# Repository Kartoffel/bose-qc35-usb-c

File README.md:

# Bose QC35 USB-C mod

This is a repository holding details of how to modify the Bose QC35 headphones
to support USB charging/firmware update over USB-C, rather than the archaic
micro-USB connector. This mod works with both QC35 I and QC35 II versions of the
headphones.

## Disclaimer

This mod involves opening and disassembing your rather expensive headphone that
you probably really like using. There is a not insignificant chance of you could
damaging your headphones in this process. Keep that in mind before you start.
For best chances of success: take your time, work on a well lit anti-static
workspace.

We don't take any responsibility nor liability for damage when using any
information provided in this repository.

Good luck!

## Quick start

### [View schematic and layout online using KiCanvas!](https://kicanvas.org/?github=https%3A%2F%2Fgithub.com%2Fjamesturton%2Fbose-qc35-usb-c)

## How to get started

You will be replacing the USB daughter board with a new one featuring a USB-C
connector. This means there is no modification to the existing USB daughter
board, thus (other than enlarging the hole in the plastic housing) this process
is easily reversible.

The exisiting USB daughter board has been reverse-engineered and it's schematic
has been drawn using KiCad 8.0. All of the source files are provided here if you
would like to make any more changes, however the [gerber files](https://github.com/jamesturton/bose-qc35-usb-c/blob/main/gerber.zip?raw=true)
are also provided which can be sent directly to the PCB fab of your choosing.
The thickness of the PCB should be 1mm.

Once you have the sent off for the PCB to be manufactured, you will need to
order the parts to populate the PCB with. Some PCB fabs offer assembly also, but
I am not sure if any 'budget' PCB fab offer double-sided assembly services.
An 'interactive BoM' can be found in the 'bom' directory.

## Assembly

Assembly of this PCB is not for the faint of heart. A decent soldering/re-work
station, microscope and experience with soldering fine-pitch components are all
recommended. The molex connector for the flat-flex to the main board has a pin
pitch of 0.4mm. I recommend starting with the passives and LEDs first, working
up to the larger ICs and connectors later.

Once you have assembled the PCB you can start to disassemble your headphones to
replace the USB daughter board:
* Remove the foam earcup and foam sheet across the speaker grill on the right
ear phone.
* Remove the three philips-0 screws holding the metal outer shell in place. This
reveals the USB daughter board and mainboard.
* Cut away the silastic holding the cable for the mainboard.
* Remove the mainboard and LED/button board cables from the USB board.
* Unscrew the two philips-0 screws holding down the USB board to remove it.

With the old USB board removed it is now time for the most destructive step. You
will need to enlarge the hole in the plastic housing for the larger USB-C
connector to exit through. This can be done easily with a rotary tool, or less
easily with a small file. Keep checking the fit with the USB-C connector so the
hole is not made too big.

Reassemble the headphones by reversing the steps above.

### Enjoy using your modded headphones!

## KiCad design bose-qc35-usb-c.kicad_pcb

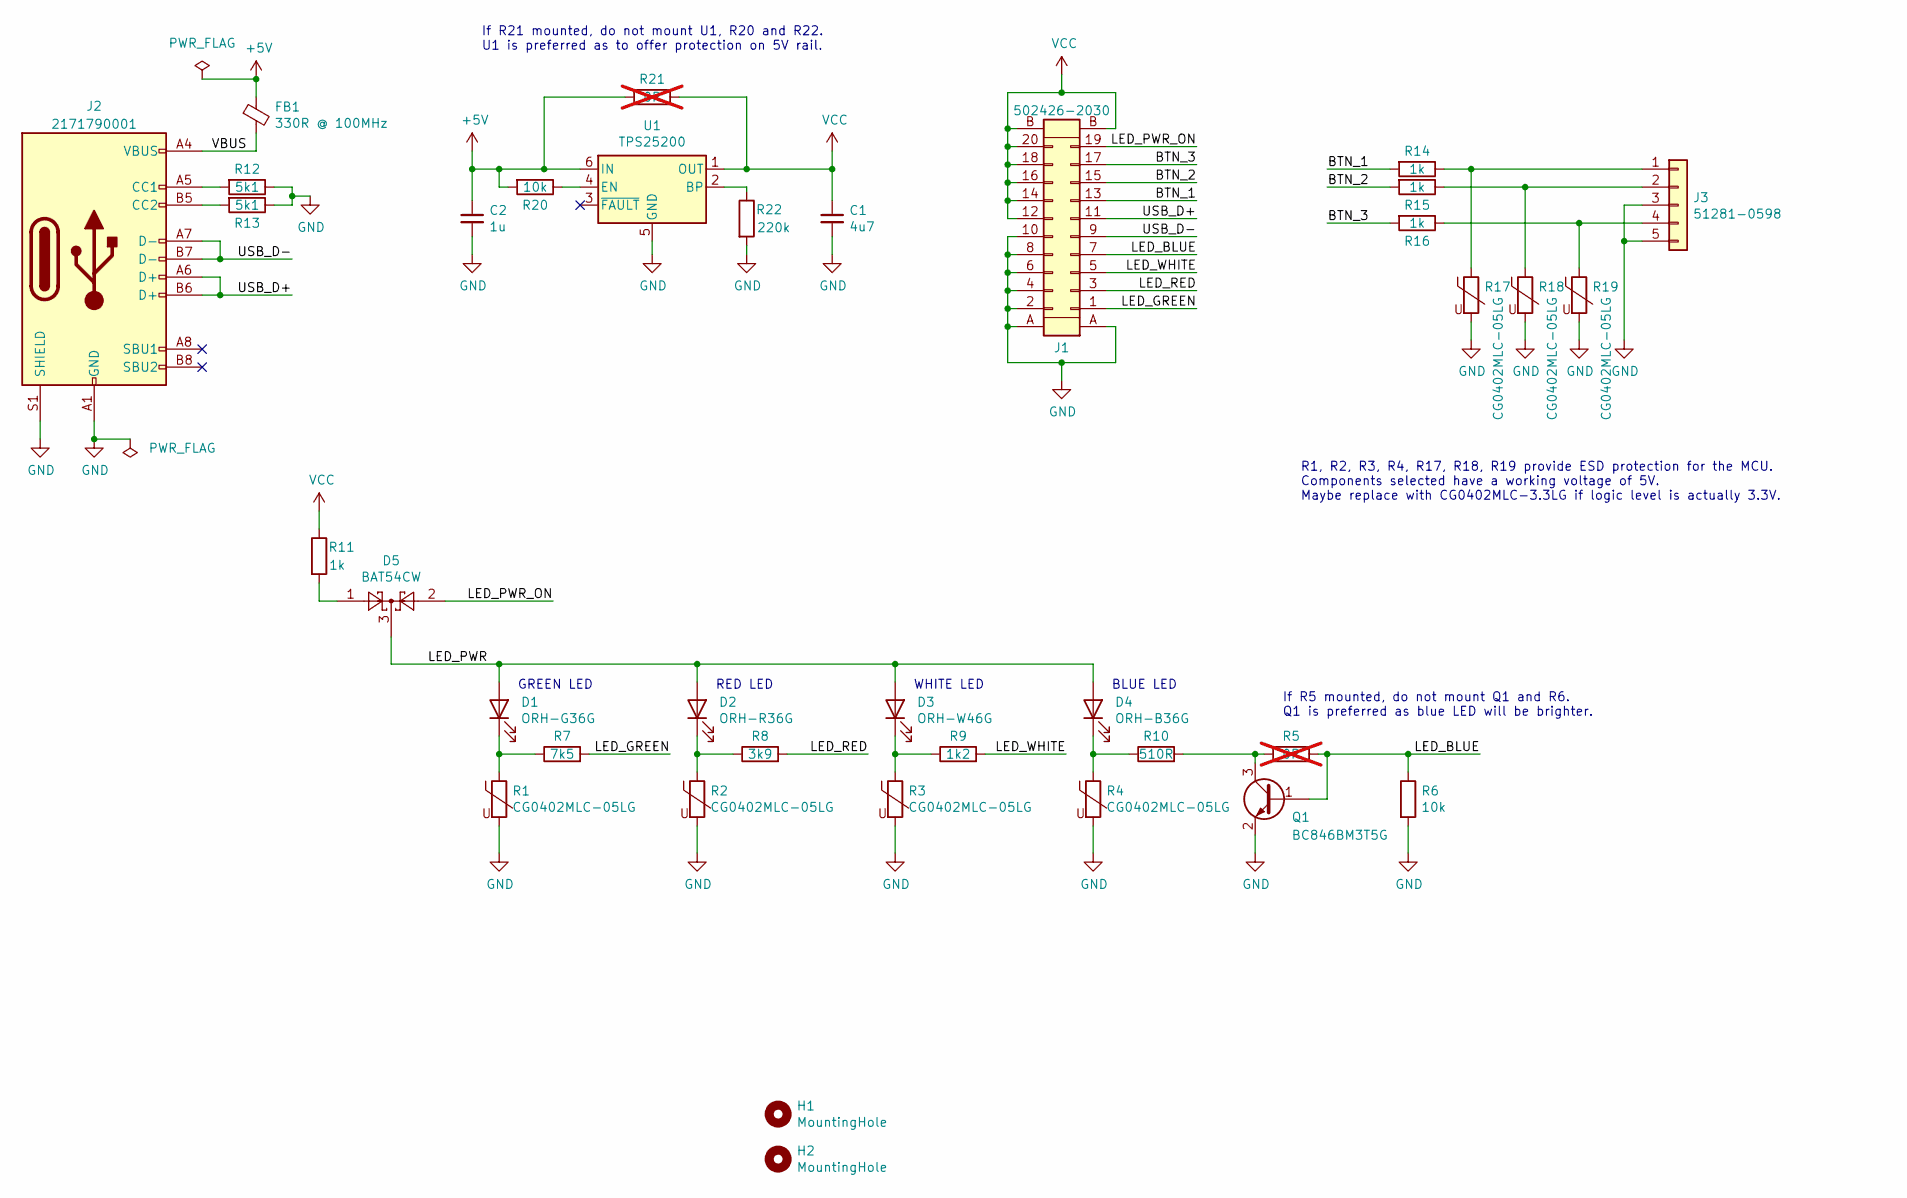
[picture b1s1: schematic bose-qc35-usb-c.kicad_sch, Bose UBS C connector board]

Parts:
C1: 4u7; C_0402_1005Metric; LCSC C23733
C2: 1u; C_0402_1005Metric; LCSC C52923
D1: ORH-G36G; LED_0603_1608Metric; LCSC C7371905
D2: ORH-R36G; LED_0603_1608Metric; LCSC C2286
D3: ORH-W46G; LED_0603_1608Metric; LCSC C2290
D4: ORH-B36G; LED_0603_1608Metric; LCSC C193191
D5: BAT54CW; SOT-323_SC-70; LCSC C22392482
FB1: 330R @ 100MHz; Fuse_0402_1005Metric; LCSC C160975
H1, H2: MountingHole; MountingHole_2.1mm
J1: 502426-2030; Molex_SlimStack_502426-2010_2x10_P0.40mm_Vertical; LCSC C563934
J2: 2171790001; USB_C_Receptacle_Molex_2171790001; LCSC C29780877
J3: 51281-0598; TE_0-1734839-5_1x05-1MP_P0.5mm_Horizontal; LCSC C18548053
Q1: BC846BM3T5G; SOT-723; LCSC C232536
R1, R2, R3, R4, R17, R18, R19: CG0402MLC-05LG; R_0402_1005Metric; LCSC C711709
R5, R21: 0R; R_0402_1005Metric; not fitted
R6, R20: 10k; R_0402_1005Metric; LCSC C25744
R7: 7k5; R_0402_1005Metric; LCSC C137934
R8: 3k9; R_0402_1005Metric; LCSC C131467
R9: 1k2; R_0402_1005Metric; LCSC C25862
R10: 510R; R_0402_1005Metric; LCSC C25123
R11, R14, R15, R16: 1k; R_0402_1005Metric; LCSC C11702
R12, R13: 5k1; R_0402_1005Metric; LCSC C25905
R22: 220k; R_0402_1005Metric; LCSC C25767
U1: TPS25200; WSON-6-1EP_2x2mm_P0.65mm_EP1x1.6mm; LCSC C128401

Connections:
+5V: C2.1, FB1.1, R20.2, R21.2, U1.6 (IN)
/BTN_1: J1.13, R14.2
/BTN_2: J1.15, R15.2
/BTN_3: J1.17, R16.2
/LED_BLUE: J1.7, Q1.1 (B), R5.2, R6.1
/LED_GREEN: J1.1, R7.2
/LED_PWR: D1.2 (A), D2.2 (A), D3.2 (A), D4.2 (A), D5.3
/LED_PWR_ON: D5.2, J1.19
/LED_RED: J1.3, R8.2
/LED_WHITE: J1.5, R9.2
/USB_D+: J1.11, J2.A6 (D+), J2.B6 (D+)
/USB_D-: J1.9, J2.A7 (D-), J2.B7 (D-)
/VBUS: FB1.2, J2.A4 (VBUS), J2.A9 (VBUS), J2.B4 (VBUS), J2.B9 (VBUS)
GND: C1.2, C2.2, J1.2, J1.4, J1.6, J1.8, J1.10, J1.A, J2.A1 (GND), J2.A12 (GND), J2.B1 (GND), J2.B12 (GND), J2.S1 (SHIELD), J3.3, J3.5, Q1.2 (E), R1.2, R2.2, R3.2, R4.2, R6.2, R12.1, R13.1, R17.2, R18.2, R19.2, R22.2, U1.5 (GND), U1.7 (GND)
unnamed: D1.1 (K), R1.1, R7.1
unnamed: D2.1 (K), R2.1, R8.1
unnamed: D3.1 (K), R3.1, R9.1
unnamed: D4.1 (K), R4.1, R10.1
unnamed: D5.1, R11.2
unnamed: J2.A5 (CC1), R12.2
unnamed: J2.B5 (CC2), R13.2
unnamed: J3.1, R14.1, R17.1
unnamed: J3.2, R15.1, R18.1
unnamed: J3.4, R16.1, R19.1
unnamed: Q1.3 (C), R5.1, R10.2
unnamed: R22.1, U1.2 (BP)
unnamed: R20.1, U1.4 (EN)
VCC: C1.1, J1.12, J1.14, J1.16, J1.18, J1.20, J1.B, R11.1, R21.1, U1.1 (OUT)

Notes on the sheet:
R1, R2, R3, R4, R17, R18, R19 provide ESD protection for the MCU. Components selected have a working voltage of 5V. Maybe replace with CG0402MLC-3.3LG if logic level is actually 3.3V.
WHITE LED
GREEN LED
RED LED
If R21 mounted, do not mount U1, R20 and R22. U1 is preferred as to offer protection on 5V rail.
If R5 mounted, do not mount Q1 and R6. Q1 is preferred as blue LED will be brighter.
BLUE LED

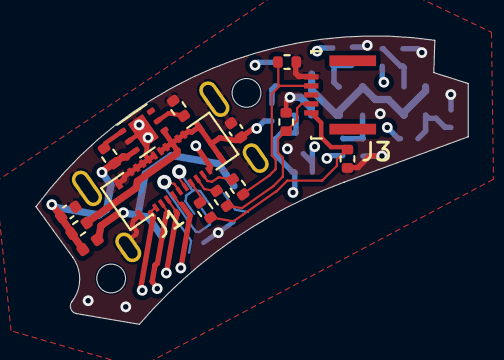
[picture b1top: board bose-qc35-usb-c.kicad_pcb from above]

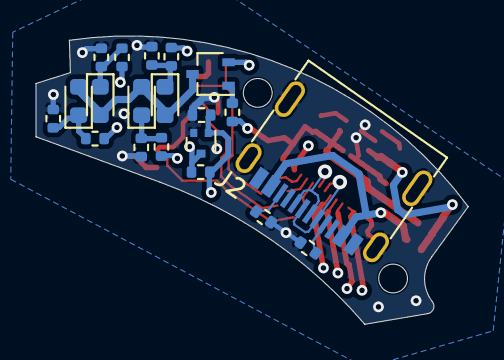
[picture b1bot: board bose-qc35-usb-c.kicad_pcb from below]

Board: 4 copper layers, 24.0 x 16.0 mm, 37 parts (20 on the bottom side), 28 nets.

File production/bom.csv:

Designator,Footprint,Quantity,Value,LCSC Part #
C1,0402,1,4u7,C23733
C2,0402,1,1u,C52923
D1,0603,1,ORH-G36G,C7371905
D2,0603,1,ORH-R36G,C2286
D3,0603,1,ORH-W46G,C2290
D4,0603,1,ORH-B36G,C193191
D5,SOT-323_SC-70,1,BAT54CW,C22392482
FB1,0402,1,330R @ 100MHz,C160975
J1,Molex_SlimStack_502426-2010_2x10_P0.40mm_Vertical,1,502426-2030,C563934
J2,USB_C_Receptacle_Molex_2171790001,1,2171790001,C29780877
J3,TE_0-1734839-5_1x05-1MP_P0.5mm_Horizontal,1,51281-0598,C18548053
Q1,SOT-723,1,BC846BM3T5G,C232536
"R1, R17, R18, R19, R2, R3, R4",0402,7,CG0402MLC-05LG,C711709
R10,0402,1,510R,C25123
"R11, R14, R15, R16",0402,4,1k,C11702
"R12, R13",0402,2,5k1,C25905
"R20, R6",0402,2,10k,C25744
R22,0402,1,220k,C25767
R7,0402,1,7k5,C137934
R8,0402,1,3k9,C131467
R9,0402,1,1k2,C25862
U1,WSON-6-1EP_2x2mm_P0.65mm_EP1x1.6mm,1,TPS25200,C128401

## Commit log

2024-12-21 Convert to KiCad 8.0
2024-12-21 Fix Molex USB-C connector footprint
    Update part origin and use correct 3D model
2024-12-21 Fix silkscreen
    Remove excess
2025-01-17 Update DNP components
2025-01-17 Remove old production files
2025-01-17 Add JLC production files

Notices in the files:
bose-qc35-usb-c.kicad_pcb:
(C) 2020 James Turton
License: CC-BY-SA 4.0
